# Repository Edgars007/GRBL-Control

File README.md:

# GRBL-Control
PCB to control three servos with GRBL. 
One Arduino reads gcode file from SD card and sends the commands to other one for execution.

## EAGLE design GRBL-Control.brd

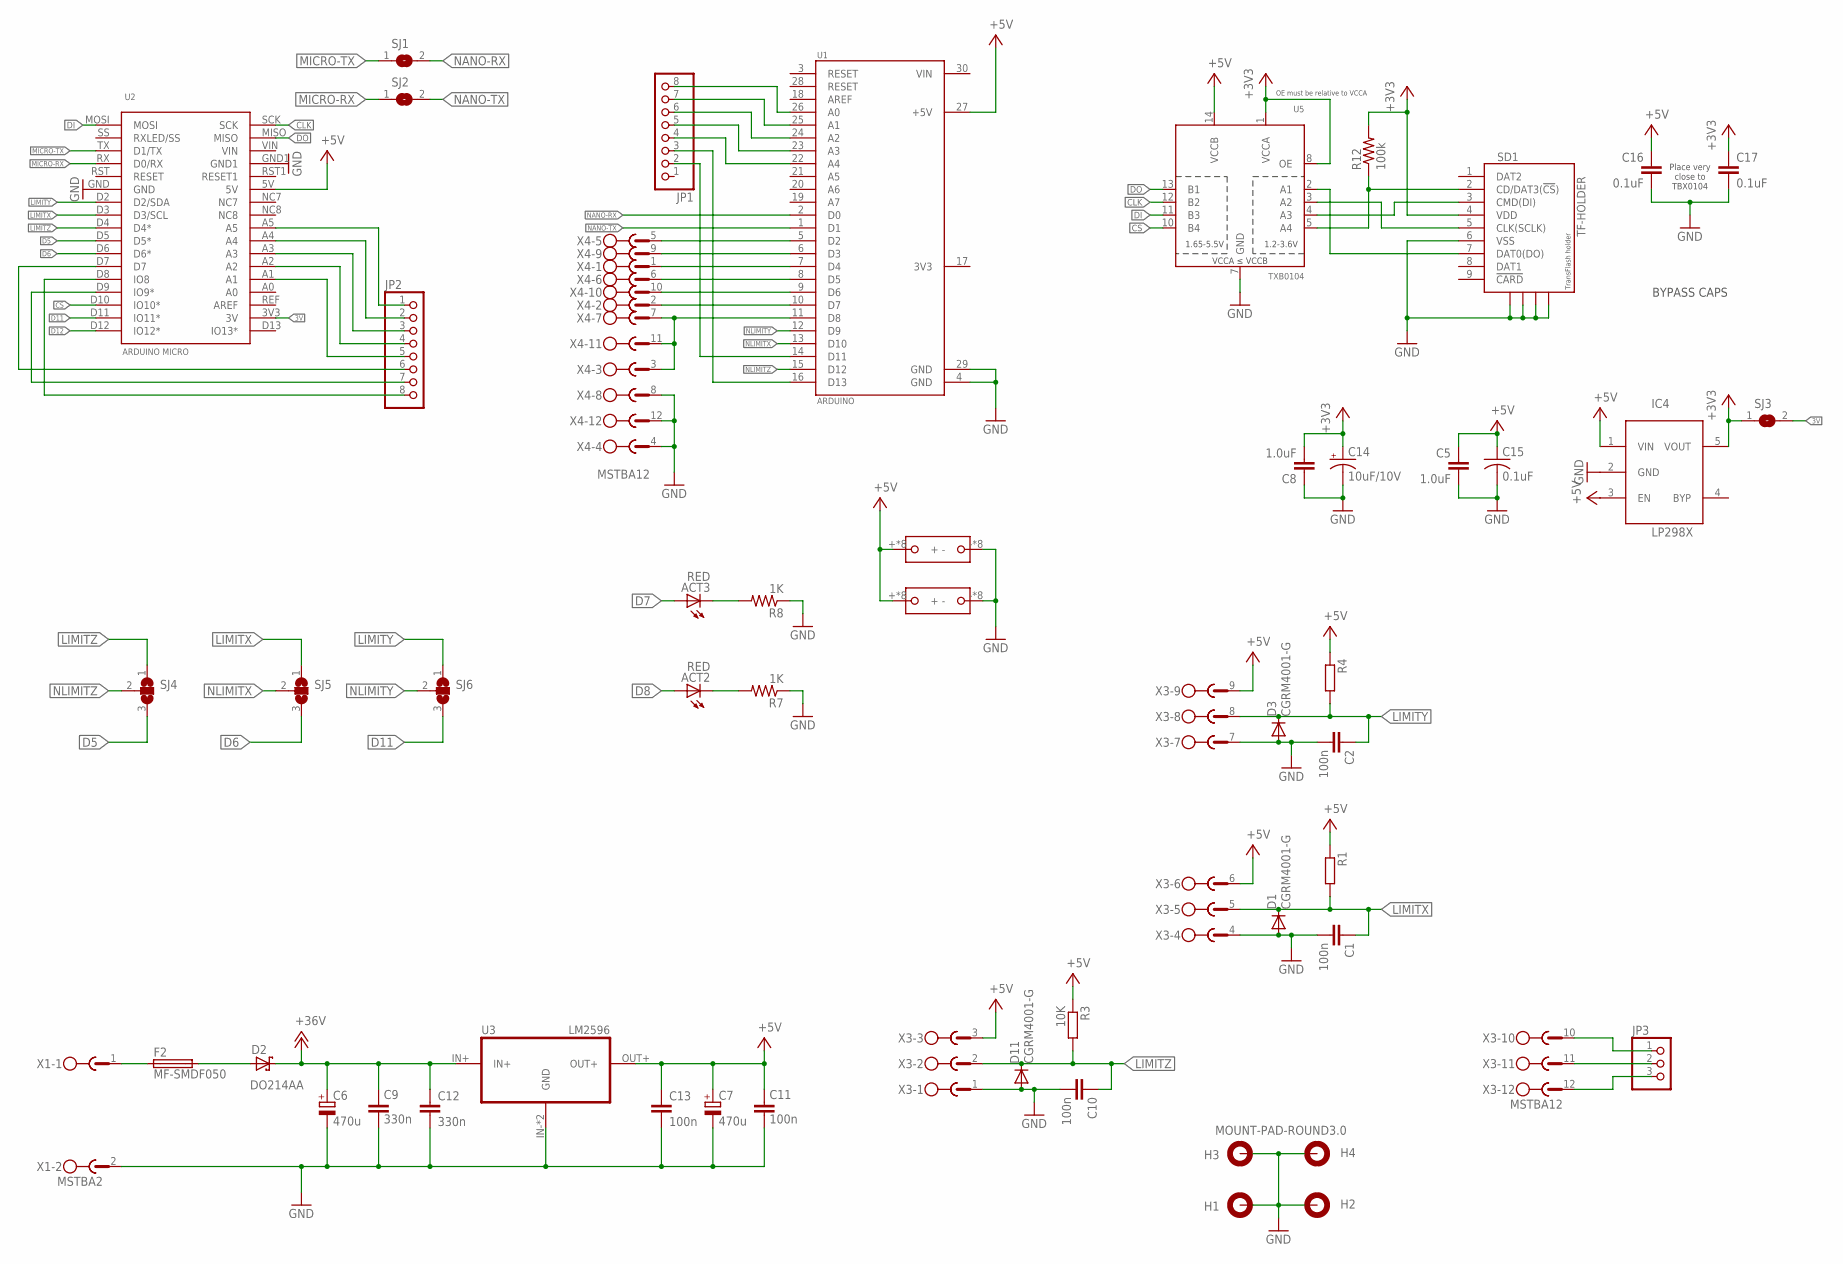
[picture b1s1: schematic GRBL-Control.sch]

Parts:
ACT2, ACT3: RED; CHIP-LED0805
C1, C2, C10, C11: 100n; C0603
C5, C8: 1.0uF; 0603-CAP
C6, C7: 470u; E3,5-8
C9: 330n; C0603
C12: 330n; C050-025X075
C13: 100n; C050-025X075
C14: 10uF/10V; A/3216-18R
C15: 0.1uF; C0805K
C16, C17: 0.1uF; 0603-CAP
D1, D3, D11: CGRM4001-G; SOD-123_MINI-SMA
D2: DO214AA; SMB; PART-NO DO214AA
F2: MF-SMDF050
H1, H2, H3, H4: MOUNT-PAD-ROUND3.0; 3,0-PAD
IC4: LP298XS; SOT23-5L
JP1, JP2: PINHD-1X8BIG; 1X08-BIG
JP3: PINHD-1X3; 1X03
R1, R4: R-EU_R0603; R0603
R3: 10K; R0603
R7, R8: 1K; R0805
R12: 100k; 0603-RES
SD1: TF-HOLDER; TF-PULL
SJ1, SJ2, SJ3: SJ
SJ4, SJ5, SJ6: SJ2W; SJ_2
U1: ARDUINO; ARDUINO_A000005
U2: ARDUINO MICRO; ARDUINO-MICRO
U3: LM2596; BUCK-LM2596
U5: TXB0104; SO14
U$1, U$2: DEV_GRID
X1: MSTBA2
X3, X4: MSTBA12

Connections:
3V: SJ3.2, U2.3V3 (3V)
12V-IN: F2.1, X1.1
!CS_3V3: R12.1, SD1.2 (CD/DAT3(!CS!)), U5.5 (A4)
+3V3: C8.2, C14.+, C17.1, IC4.5 (VOUT), R12.2, SD1.4 (VDD), SJ3.1, U5.1 (VCCA), U5.8 (OE)
+5V: C5.1, C7.+, C11.1, C13.1, C15.1, C16.1, IC4.1 (VIN), IC4.3 (EN), R1.1, R3.1, R4.1, U1.27 (+5V), U2.5V, U3.OUT+, U5.14 (VCCB), U$1.+, U$1.P$49 (+), U$1.P$50 (+), U$1.P$51 (+), U$1.P$52 (+), U$1.P$53 (+), U$1.P$54 (+), U$1.P$55 (+), U$2.+, U$2.P$49 (+), U$2.P$50 (+), U$2.P$51 (+), U$2.P$52 (+), U$2.P$53 (+), U$2.P$54 (+), U$2.P$55 (+), X3.3, X3.6, X3.9
+36V: C6.+, C9.1, C12.1, D2.C, U3.IN+
A1: JP2.5, U2.A1
A2: JP2.4, U2.A2
A3: JP2.3, U2.A3
A4: JP2.2, U2.A4
A5: JP2.1, U2.A5
CLK: U2.SCK, U5.12 (B2)
CLK_3V3: SD1.5 (CLK(SCLK)), U5.3 (A2)
CS: U2.D10 (IO10*), U5.10 (B4)
D5: SJ4.3, U2.D5 (D5*)
D6: SJ5.3, U2.D6 (D6*)
D7: ACT3.A, JP2.6, U2.D7
D8: ACT2.A, JP2.8, U2.D8 (IO8)
D9: JP2.7, U2.D9 (IO9*)
D11: SJ6.3, U2.D11 (IO11*)
D12: U2.D12 (IO12*)
DI: U2.MOSI, U5.11 (B3)
DIRX: U1.8 (D5), X4.6
DIRY: U1.9 (D6), X4.10
DI_3V3: SD1.3 (CMD(DI)), U5.4 (A3)
DO: U2.MISO, U5.13 (B1)
DO_3V3: SD1.7 (DAT0(DO)), U5.2 (A1)
GND: C1.2, C2.2, C5.2, C6.-, C7.-, C8.1, C9.2, C10.2, C11.2, C12.2, C13.2, C14.-, C15.2, C16.2, C17.2, D1.A, D3.A, D11.A, H1.B3,0, H1.P$1, H1.P$2, H1.P$3, H1.P$4, H1.P$5, H1.P$6, H1.P$7, H1.P$8, H2.B3,0, H2.P$1, H2.P$2, H2.P$3, H2.P$4, H2.P$5, H2.P$6, H2.P$7, H2.P$8, H3.B3,0, H3.P$1, H3.P$2, H3.P$3, H3.P$4, H3.P$5, H3.P$6, H3.P$7, H3.P$8, H4.B3,0, H4.P$1, H4.P$2, H4.P$3, H4.P$4, H4.P$5, H4.P$6, H4.P$7, H4.P$8, IC4.2 (GND), R7.1, R8.1, SD1.6 (VSS), SD1.S1, SD1.S2, SD1.S3, SD1.S4, U1.4 (GND), U1.29 (GND), U2.GND, U2.GND1, U3.IN- (GND), U3.OUT- (GND), U5.7 (GND), U$1.-, U$1.P$57 (-), U$1.P$58 (-), U$1.P$59 (-), U$1.P$60 (-), U$1.P$61 (-), U$1.P$62 (-), U$1.P$63 (-), U$2.-, U$2.P$57 (-), U$2.P$58 (-), U$2.P$59 (-), U$2.P$60 (-), U$2.P$61 (-), U$2.P$62 (-), U$2.P$63 (-), X1.2, X3.1, X3.4, X3.7, X4.4, X4.8, X4.12
LIMITX: C1.1, D1.C, R1.2, SJ5.1, U2.D3 (D3/SCL), X3.5
LIMITY: C2.1, D3.C, R4.2, SJ6.1, U2.D2 (D2/SDA), X3.8
LIMITZ: C10.1, D11.C, R3.2, SJ4.1, U2.D4 (D4*), X3.2
MICRO-RX: SJ2.1, U2.RX (D0/RX)
MICRO-TX: SJ1.1, U2.TX (D1/TX)
unnamed: ACT2.C, R7.2
unnamed: ACT3.C, R8.2
unnamed: D2.A, F2.2
unnamed: U1.7 (D4), X4.1
unnamed: U1.10 (D7), X4.2
unnamed: JP1.8, U1.26 (A0)
unnamed: JP1.7, U1.25 (A1)
unnamed: JP1.6, U1.24 (A2)
unnamed: JP1.5, U1.23 (A3)
unnamed: JP1.4, U1.22 (A4)
unnamed: JP1.3, U1.16 (D13)
unnamed: JP1.2, U1.14 (D11)
unnamed: JP3.1, X3.10
unnamed: JP3.2, X3.11
unnamed: JP3.3, X3.12
NANO-RX: SJ1.2, U1.2 (D0)
NANO-TX: SJ2.2, U1.1 (D1)
NLIMITX: SJ5.2, U1.13 (D10)
NLIMITY: SJ6.2, U1.12 (D9)
NLIMITZ: SJ4.2, U1.15 (D12)
STEP-EN: U1.11 (D8), X4.3, X4.7, X4.11
STEPX: U1.5 (D2), X4.5
STEPY: U1.6 (D3), X4.9
VIN: U1.30 (VIN)

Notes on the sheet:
Place very close to TBX0104
OE must be relative to VCCA
BYPASS CAPS

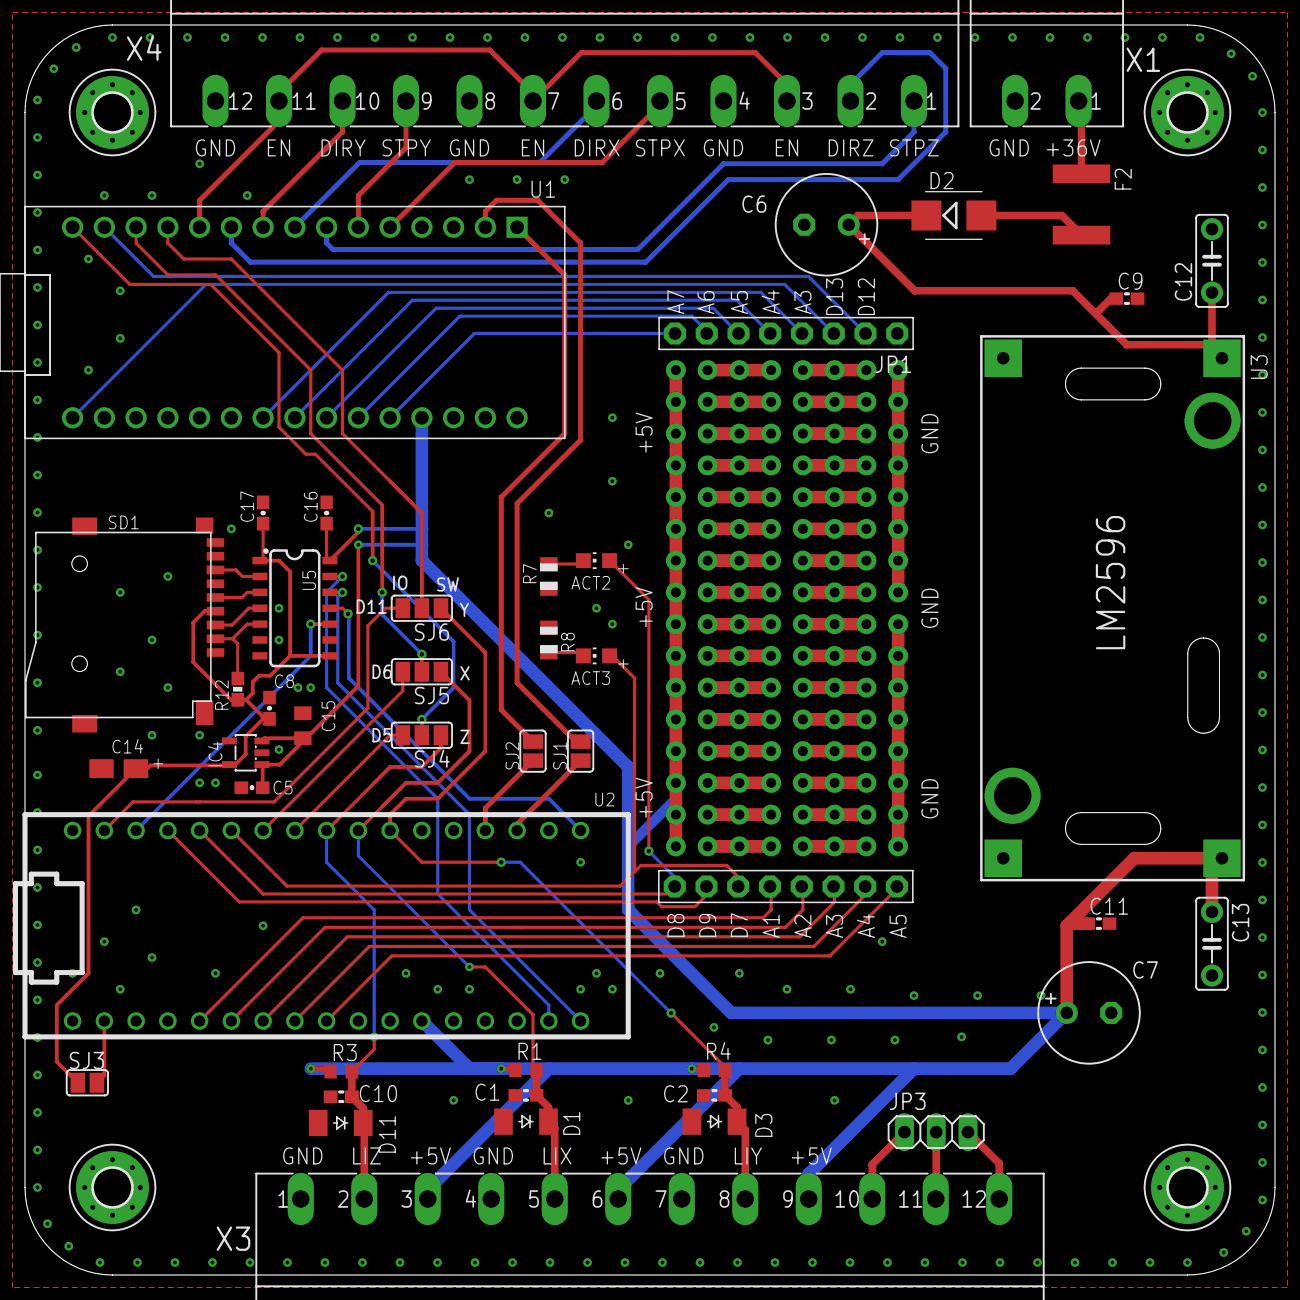
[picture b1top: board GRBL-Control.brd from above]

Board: 2 copper layers, 100.0 x 100.0 mm, 52 parts (0 on the bottom side), 55 nets.

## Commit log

2020-10-19 v1.1 changed level converter for SD card, added soldering place and some other minor changes

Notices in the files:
parts and their libraries:
SparkFun-Resistors: Licensing: Creative Commons ShareAlike 4.0 International - https://creativecommons.org/licenses/by-sa/4.0
